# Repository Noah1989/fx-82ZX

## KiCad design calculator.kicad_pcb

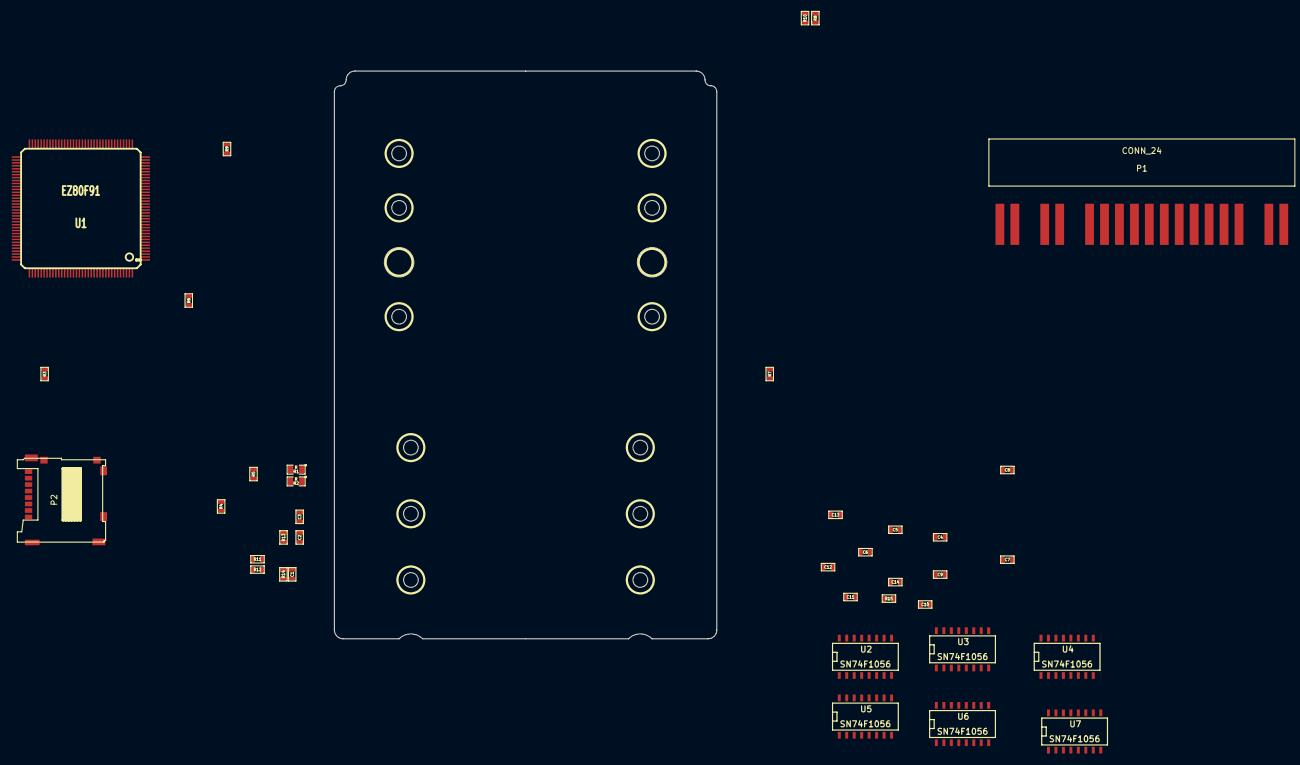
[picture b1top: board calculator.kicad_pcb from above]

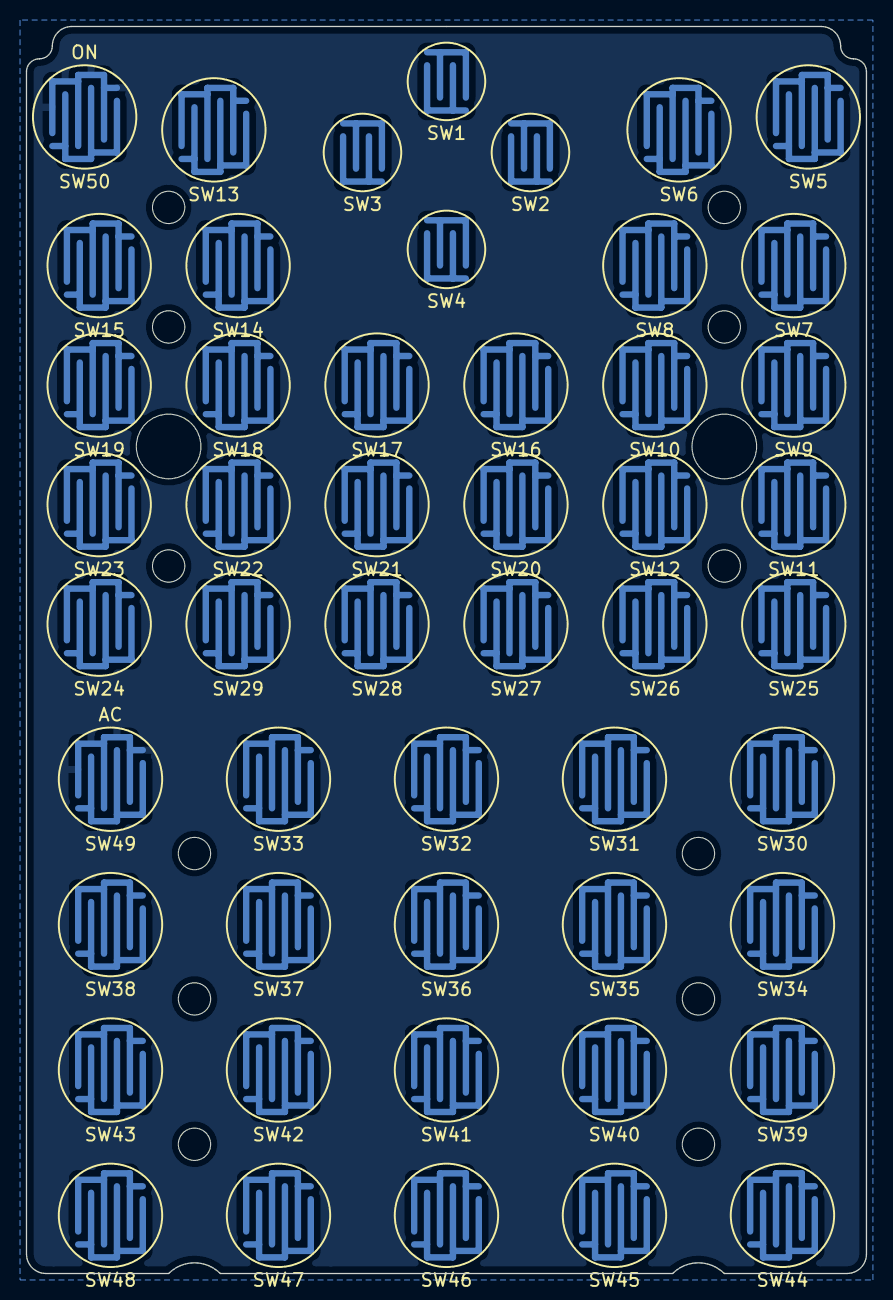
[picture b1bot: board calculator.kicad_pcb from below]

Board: 2 copper layers, 65.0 x 96.5 mm, 102 parts (50 on the bottom side), 84 nets, no tracks yet.

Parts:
1PIN, 1PIN#2, 1PIN#3, 1PIN#4, 1PIN#5, 1PIN#6, 1PIN#7, 1PIN#8, 1PIN#9, 1PIN#10, 1PIN#11, 1PIN#12, 1PIN#13, 1PIN#14: P***; 1pin
C1, C2, C3, C4, C5, C6, C7, C8, C9, C10, C11, C12, C13: 10nF; SM0603
C14: C; SM0603
P1: CONN_24; connflat
P2: CONN_10; MICROSD
R1, R2: R; SM0805
R3, R4, R5, R6, R7, R8, R9, R10, R11, R12, R13, R14, R15: R; SM0603
SW1, SW2, SW3, SW4: KEYSMALL
SW5, SW6, SW7, SW8, SW9, SW10, SW11, SW12, SW13, SW14, SW15, SW16, SW17, SW18, SW19, SW20, SW21, SW22, SW23, SW24, SW25, SW26, SW27, SW28, SW29, SW30, SW31, SW32, SW33, SW34, SW35, SW36, SW37, SW38, SW39, SW40, SW41, SW42, SW43, SW44, SW45, SW46, SW47, SW48: KEY
SW49: AC; KEY
SW50: ON; KEY
U1: EZ80F91; TQFP144
U2, U3, U4, U5, U6, U7: SN74F1056; SO16N

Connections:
/CS0: P1.8, U1.33
/CSS: P2.2, U1.100
/D0: P1.13, U1.39
/D1: P1.14, U1.40
/D3: P1.16, U1.42
/D4: P1.17, U1.43
/D6: P1.19, U1.45
/D7: P1.20, U1.46
/DC: P1.10, U1.1
/DI: P2.3, U1.107
/DO: P2.7, U1.106
/RD: P1.12, U1.51
/RES: P1.9, R1.1, SW50.1, U1.55
/SCK: P2.5, U1.103
/SW: P2.9, R13.2, U1.104
/WR: P1.11, U1.52
unnamed: P2.1, R11.1
unnamed: P2.8, R12.1
unnamed: R14.2, U1.102
unnamed: R7.2, SW19.2, SW20.2, SW21.2, SW22.2, SW23.2, SW24.2, U1.118
unnamed: R8.2, SW13.2, SW14.2, SW15.2, SW16.2, SW17.2, SW18.2, U1.119
unnamed: R9.2, SW7.2, SW8.2, SW9.2, SW10.2, SW11.2, SW12.2, U1.120
unnamed: R2.1, SW49.1, U1.56
unnamed: U1.96, U6.10, U6.11, U6.12, U6.13, U6.14, U6.15
unnamed: SW6.1, U7.1
unnamed: SW12.1, U7.2
unnamed: SW18.1, U7.3
unnamed: SW24.1, U7.4
unnamed: SW30.1, U7.5
unnamed: SW36.1, U7.6
unnamed: SW42.1, U7.7
unnamed: SW48.1, U7.8
unnamed: U1.97, U7.10, U7.11, U7.12, U7.13, U7.14, U7.15
unnamed: R5.1, SW31.2, SW32.2, SW33.2, SW34.2, SW35.2, SW36.2, U1.116
unnamed: R6.1, SW25.2, SW26.2, SW27.2, SW28.2, SW29.2, SW30.2, U1.117
unnamed: R10.2, SW1.2, SW2.2, SW3.2, SW4.2, SW5.2, SW6.2, U1.121
unnamed: R3.1, SW43.2, SW44.2, SW45.2, SW46.2, SW47.2, SW48.2, U1.114
unnamed: R4.1, SW37.2, SW38.2, SW39.2, SW40.2, SW41.2, SW42.2, U1.115
unnamed: U1.92, U2.10, U2.11, U2.12, U2.13, U2.14, U2.15
unnamed: U1.93, U3.10, U3.11, U3.12, U3.13, U3.14, U3.15
unnamed: U1.94, U4.10, U4.11, U4.12, U4.13, U4.14, U4.15
unnamed: U1.95, U5.10, U5.11, U5.12, U5.13, U5.14, U5.15
unnamed: SW45.1, U4.8
unnamed: SW46.1, U5.8
unnamed: SW47.1, U6.8
unnamed: SW27.1, U4.5
unnamed: SW28.1, U5.5
unnamed: SW29.1, U6.5
unnamed: SW19.1, U2.4
unnamed: SW20.1, U3.4
unnamed: SW21.1, U4.4
unnamed: SW26.1, U3.5
unnamed: SW23.1, U6.4
unnamed: SW13.1, U2.3
unnamed: SW14.1, U3.3
unnamed: SW10.1, U5.2
unnamed: SW8.1, U3.2
unnamed: SW17.1, U6.3
unnamed: SW35.1, U6.6
unnamed: SW43.1, U2.8
unnamed: SW44.1, U3.8
unnamed: SW31.1, U2.6
unnamed: SW32.1, U3.6
unnamed: SW33.1, U4.6
unnamed: SW34.1, U5.6
unnamed: SW37.1, U2.7
unnamed: SW38.1, U3.7
unnamed: SW39.1, U4.7
unnamed: SW40.1, U5.7
unnamed: SW41.1, U6.7
unnamed: SW25.1, U2.5
unnamed: SW1.1, U2.1
unnamed: SW7.1, U2.2
unnamed: SW4.1, U5.1
unnamed: SW16.1, U5.3
unnamed: SW22.1, U5.4
unnamed: SW5.1, U6.1
unnamed: SW11.1, U6.2
unnamed: SW2.1, U3.1
unnamed: SW3.1, U4.1
unnamed: SW9.1, U4.2
unnamed: SW15.1, U4.3
VDD: C1.1, C2.1, C3.1, C4.1, C5.1, C6.1, C7.1, C8.1, C9.1, C10.1, C11.1, C12.1, C13.1, P1.5, P1.6, P1.7, P2.4, R1.2, R2.2, R11.2, R12.2, R13.1, R14.1, U1.6, U1.14, U1.22, U1.31, U1.37, U1.47, U1.59, U1.81, U1.88, U1.98, U1.112, U1.122, U1.133
VSS: C1.2, C2.2, C3.2, C4.2, C5.2, C6.2, C7.2, C8.2, C9.2, C10.2, C11.2, C12.2, C13.2, C14.2, P1.1, P1.2, P2.6, P2.10, R3.2, R4.2, R5.2, R6.2, R7.1, R8.1, R9.1, R10.1, R15.1, SW49.2, SW50.2, U1.7, U1.15, U1.23, U1.32, U1.38, U1.48, U1.60, U1.64, U1.72, U1.82, U1.89, U1.99, U1.108, U1.113, U1.123, U1.134

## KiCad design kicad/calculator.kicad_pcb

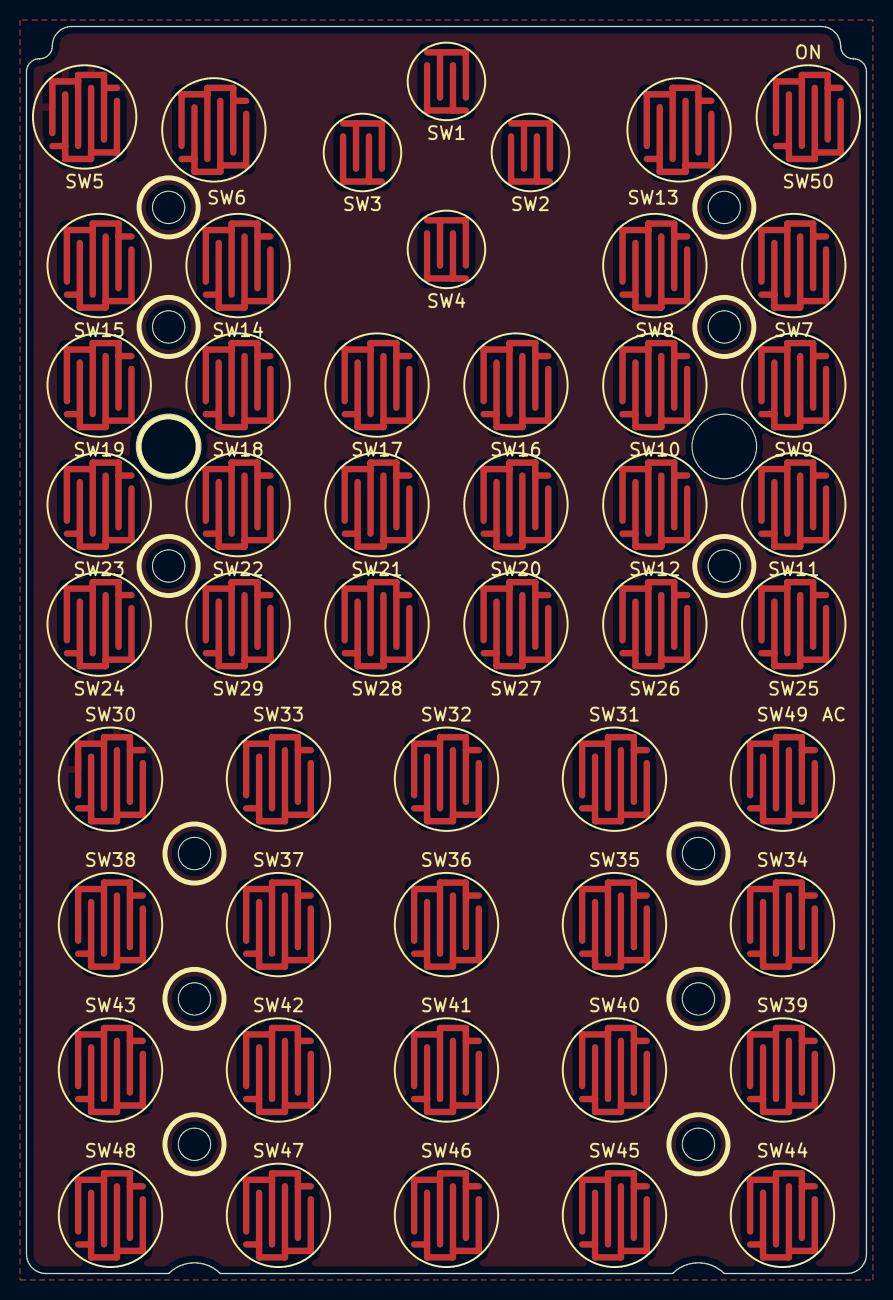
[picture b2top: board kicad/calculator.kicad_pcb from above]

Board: 2 copper layers, 65.0 x 96.5 mm, 64 parts (1 on the bottom side), 9 nets, no tracks yet.

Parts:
1PIN, 1PIN#2, 1PIN#3, 1PIN#4, 1PIN#5, 1PIN#6, 1PIN#7, 1PIN#8, 1PIN#9, 1PIN#10, 1PIN#11, 1PIN#12, 1PIN#13, 1PIN#14: P***; 1pin
SW1, SW2, SW3, SW4: KEYSMALL
SW5, SW6, SW7, SW8, SW9, SW10, SW11, SW12, SW13, SW14, SW15, SW16, SW17, SW18, SW19, SW20, SW21, SW22, SW23, SW24, SW25, SW26, SW27, SW28, SW29, SW30, SW31, SW32, SW33, SW34, SW35, SW36, SW37, SW38, SW39, SW40, SW41, SW42, SW43, SW44, SW45, SW46, SW47, SW48: KEY
SW49: AC; KEY
SW50: ON; KEY

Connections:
unnamed: SW43.2, SW44.2, SW45.2, SW46.2, SW47.2, SW48.2
unnamed: SW37.2, SW38.2, SW39.2, SW40.2, SW41.2, SW42.2
unnamed: SW31.2, SW32.2, SW33.2, SW34.2, SW35.2, SW36.2
unnamed: SW25.2, SW26.2, SW27.2, SW28.2, SW29.2, SW30.2
unnamed: SW19.2, SW20.2, SW21.2, SW22.2, SW23.2, SW24.2
unnamed: SW13.2, SW14.2, SW15.2, SW16.2, SW17.2, SW18.2
unnamed: SW7.2, SW8.2, SW9.2, SW10.2, SW11.2, SW12.2
unnamed: SW1.2, SW2.2, SW3.2, SW4.2, SW5.2, SW6.2
unnamed: SW49.2, SW50.2

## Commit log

2014-04-27 added missing files
2016-05-15 remove old components, fix PCB orientation
2016-06-24 added lots of stuff to the schematic
2016-07-19 add more circuitry to schematic
2016-07-19 move kicad stuff into subdirectory
2016-07-19 add C project in system directory
2016-07-20 add travis config
2016-07-20 specify compiler, lower cmake version, add .gitignore
2016-07-20 travis: install sdcc
2016-07-20 travis: show sdcc version
2016-07-20 travis: use trusty
2016-07-20 use provided include files from sdcc (just discovered lint.h)
2016-07-26 kprintf (dummy)
